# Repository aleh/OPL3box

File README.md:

# OPL3box

This is about controlling an old OPL3 chip as a regular synth via MIDI. Work in progress.

You need to have [a21](https://github.com/aleh/a21) library installed in your Arduino environment.
Sketch > Include Library > Manage Libraries

## Schematics

See `kicad` folder for the most up-to-date version. Here is one as a PNG:

## PCB

See `kicad` folder.

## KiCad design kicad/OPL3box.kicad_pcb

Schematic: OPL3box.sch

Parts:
C1, C2, C8, C13: 100n; C_Disc_D4.7mm_W2.5mm_P5.00mm
C3: 100p; C_Disc_D4.7mm_W2.5mm_P5.00mm
C4, C5: 20p; C_Disc_D4.7mm_W2.5mm_P5.00mm
C6: TODO: 100n; C_Disc_D4.7mm_W2.5mm_P5.00mm
C7, C9: 10uF*; CP_Radial_D4.0mm_P2.00mm
C10: 68pF; C_Disc_D4.7mm_W2.5mm_P5.00mm
C11, C12: 2700pF; C_Disc_D4.7mm_W2.5mm_P5.00mm
C14, C15: 47uF*; CP_Radial_D4.0mm_P2.00mm
C16, C17: 10uF; CP_Radial_D4.0mm_P2.00mm
D1: BAT41; D_DO-35_SOD27_P7.62mm_Horizontal
J1: MIDI-IN; PROTO_MIDI
J2: 6-12V DC; BARREL_JACK
J3: Line Out; JACK_TRS
Q1: 2N3904; TO-92_Molded_Narrow
R1: 200; R_Axial_DIN0207_L6.3mm_D2.5mm_P7.62mm_Horizontal
R2: 1K; R_Axial_DIN0207_L6.3mm_D2.5mm_P7.62mm_Horizontal
R3: 5K1; R_Axial_DIN0207_L6.3mm_D2.5mm_P7.62mm_Horizontal
R4: 100K; R_Axial_DIN0204_L3.6mm_D1.6mm_P2.54mm_Vertical
R5: 1K; R_Axial_DIN0204_L3.6mm_D1.6mm_P2.54mm_Vertical
R6: 33; R_Axial_DIN0207_L6.3mm_D2.5mm_P2.54mm_Vertical
R7, R8: 10K; R_Axial_DIN0207_L6.3mm_D2.5mm_P2.54mm_Vertical
R9, R10: 10; R_Axial_DIN0207_L6.3mm_D2.5mm_P2.54mm_Vertical
RV1: 100K; Potentiometer_Trimmer_Bourns_3266P
SW1: Encoder; EC11_ENCODER
U1: Arduino_Pro_Micro; Adruino_Pro_Micro
U2: 6N138; DIP-8_W7.62mm
U3: 128x32_OLED; OLED_128x32
U4: OPL3_YMF262_M; SOIC-24W_7.5x15.4mm_Pitch1.27mm
U5: YAC512; SOIC-16W_5.3x10.2mm_Pitch1.27mm
U6: TL074; DIP-14_W7.62mm
Y1: 14.31818 MHz; Crystal_HC49-4H_Vertical

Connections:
+5V: C1.1, C2.1, C7.1, C8.1, Q1.3, R3.1, R4.1, RV1.1, U1.21, U2.8, U3.2, U4.1, U4.7, U5.1, U5.3, U5.6, U5.9
A0: U1.18, U4.4
A1: U1.17, U4.5
D0: U1.15, U4.10
D1: U1.13, U4.11
D2: U1.12, U4.13
D3: U1.11, U4.14
D4: U1.10, U4.15
D5: U1.9, U4.16
D6: U1.8, U4.17
D7: U1.7, U4.18
ENCA: SW1.A, U1.19
ENCB: SW1.B, U1.20
ENCSW: SW1.S1, U1.14
GND: C1.2, C2.2, C3.2, C5.2, C7.2, C8.2, C9.2, C10.2, C11.2, C12.2, C13.2, C16.2, C17.2, J2.2, J3.S, R2.2, R5.2, R7.1, R8.2, RV1.3, SW1.C, SW1.S2, U1.3, U1.4, U1.23, U2.5, U3.1, U4.12, U5.2, U6.11 (V-)
MIDIIN: R3.2, U1.2, U2.6
unnamed: C3.1, Y1.2
unnamed: C4.1, Q1.2, R4.2, Y1.1
unnamed: C4.2, C5.1, C6.2, Q1.1, R5.1
unnamed: C9.1, U5.16, U6.5 (+)
unnamed: C10.1, U5.13, U6.3 (+)
unnamed: C11.1, U5.10, U6.10 (+)
unnamed: C12.1, U5.11, U6.12 (+)
unnamed: C14.1, U6.8, U6.9 (-)
unnamed: C14.2, R7.2, R9.2
unnamed: C15.1, U6.13 (-), U6.14
unnamed: C15.2, R8.1, R10.2
unnamed: C16.1, J3.T, R9.1
unnamed: C17.1, J3.R, R10.1
unnamed: D1.2, J2.1
unnamed: J1.4, U2.2
unnamed: J1.5, R1.2
unnamed: R1.1, U2.3
unnamed: R2.1, U2.7
unnamed: R6.1, U5.12
unnamed: R6.2, U6.1, U6.2 (-)
unnamed: U4.19, U5.7
unnamed: U4.20, U5.8
unnamed: U4.21, U5.4
unnamed: U4.23, U5.5
unnamed: U5.14, U6.6 (-), U6.7
OPLCLK: C6.1, RV1.2, U4.24
SCK: U1.5, U3.3
SDA: U1.6, U3.4
VIN: C13.1, D1.1, U1.24, U6.4 (V+)
WR#: U1.16, U4.6, U4.8

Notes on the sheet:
Dirty clock generator
Optional power jack
Optional MIDI input
Optional display and encoder

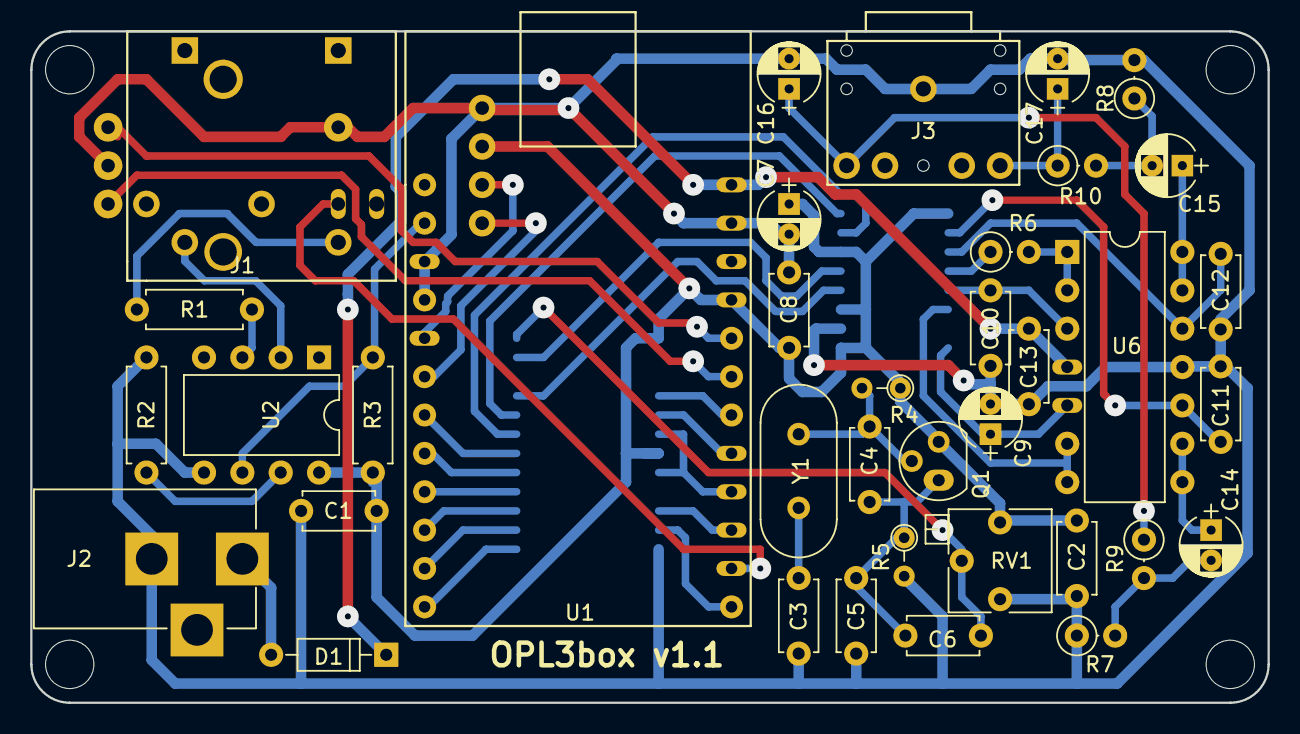
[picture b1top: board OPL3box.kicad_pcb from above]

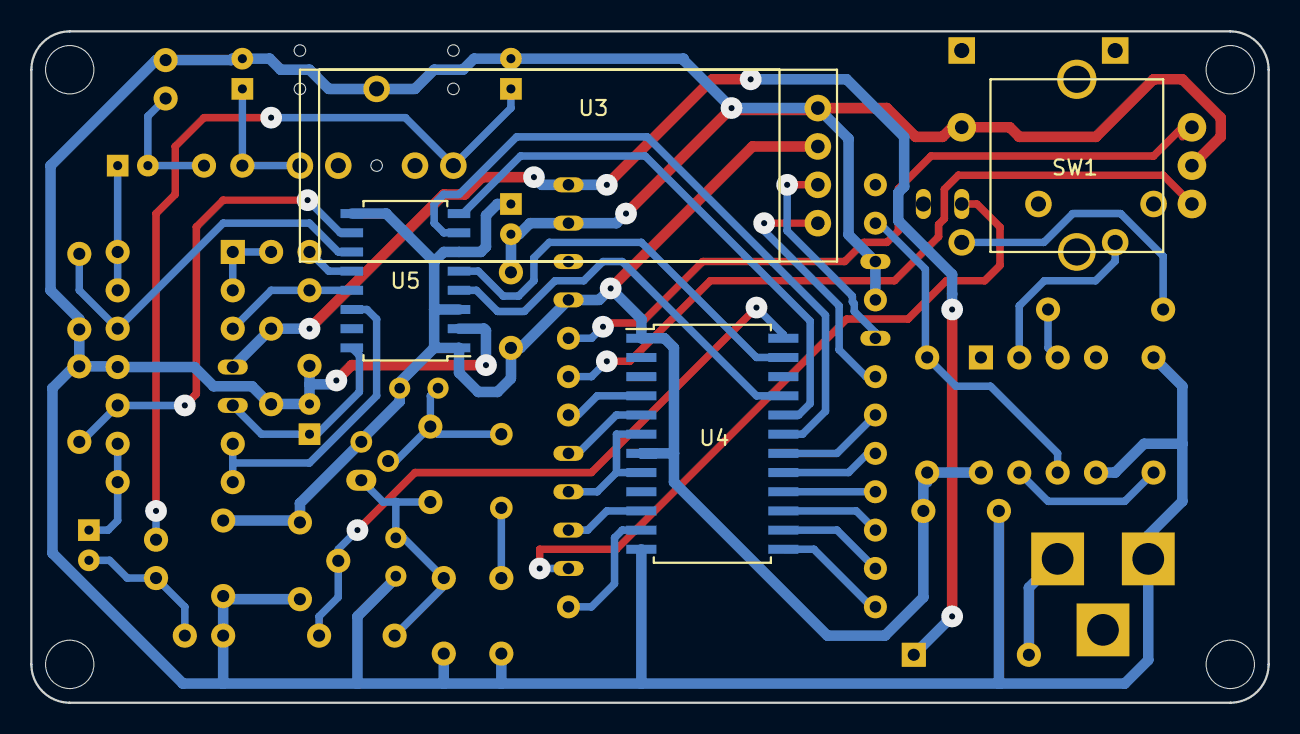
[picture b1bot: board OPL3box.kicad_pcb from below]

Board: 2 copper layers, 81.9 x 44.5 mm, 41 parts (4 on the bottom side), 46 nets.

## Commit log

2018-10-11 Test Arduino sketch
2018-10-11 KiCad files
2018-10-11 Add schematics as a PNG
2018-10-22 Added a simplistic menu system, and menus for the first operator parameters
2018-10-25 Changes to make the codebase compilable with clang
2018-10-25 Do not use static string literals for parameters name
2018-10-25 Grouping operator values together
2018-10-25 Adding the second operator values to the ui
2018-10-26 Send operators updated via the UI to the chip
2018-10-26 Cosmetic tweaks and stop changing the channel mask
2018-10-27 Reduce flickering while drawing
    (Still can flicker if frames are redrawn faster than the actual refresh rate of the LCD.)
2018-10-27 fixup! Reduce flickering while drawing
2019-10-20 PCB: fix the flipped the MIDI connector issue
